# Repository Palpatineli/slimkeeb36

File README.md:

# Slimkeeb 36 wireless split ergo keyboard

This repo contains the PCB design files and the 3d printed case file for the keyboard.
You can find the firmware at [repo](https://github.com/Palpatineli/slimkeeb36-firmware).
In the [release page](https://github.com/Palpatineli/slimkeeb36/releases/latest) you can find the pre-compiled gerber file, the stl model file and the configured 3mf file.
For the keycap used in the above photo, I am using [CLP](https://github.com/vvhg1/clp-keycaps) which is similar to chicago steno.
However you can use any low profile mx keycap you like.

## Why

Compared to existing ergo keyboards, Slimkeeb36 can be a portable, beginner friendly, and cheap choice:

1. Portable. Slim 36-key wireless design, has a built-in travel mode with no need for cases.
2. Easy to assemble and repair. Diodeless. All parts on one side of pcb.
3. Long battery life
    - Seeed xiao + 10440 battery provides long battery life at low cost
4. More column stagger and protruding thumb cluster for extra ergonomics. Choc V2 switches offer more smooth options compared to choc V1.
5. Cheap for its features:
    - Minimal parts requirement. No diodes, no buttons, no screws or insets.
    - Double sided pcb, under 100x100mm, no castellation. Can be ordered on jlcpcb for <$3 per batch (excluding shipping and tariff).
    - Case can be easily printed at home.

## What

1. Download the gerber file or export from kicad files.
Make you PCB with online PCB vendors, such as [pcbway](https://www.pcbway.com/) or [jlcpcb](https://jlcpcb.com/).
The same PCB design works for both left and right halves.
Follow vendor's guide on gerber export [such as](https://www.pcbway.com/helpcenter/generate_gerber/Generate_Gerber_file_from_Kicad.html), since the format requirement can be different.
2. Order the following:
    - Your switches and keycaps.
    - 10440 battery X2 (not AAA! 10440 are 3.7V rechargeable batteries in the same form factor as AAA). I am using [these ones](https://www.amazon.com/Rechargeable-Battery-JESSPOW-Batteries-Flashlight/dp/B08H4RC1Y5).
    - Choc hotswap sockets X36, [such as](https://www.amazon.com/Mechkeeb-Kailh-Low-Hot-swappable-Socket/dp/B0BS3JYJJQ). It's the same one for choc v1 and v2.
    - Seeed Xiao nrf52840 X2, [such as](https://www.amazon.com/XIAO-nRF52840-3PCS-Pack-CircuitPython/dp/B0DJ6NZVJT). Make sure it's nrf52840 or BLE, not BLE sense or BLE plus. Do not buy the pre-soldered ones.
    - Some 24AWG stranded wire.
    - Some electric tape.
3. Tools you will need:
    - Soldering iron
    - Multimeter
    - Soldering wire or paste. Paste is probably easier for beginners. Use the small tip on the iron if you use paste.
    - Toothpicks or small tip tweezers
    - Scissors
    - Super glue
    - USB data cable
    - A basic FDM 3d printer, 0.4mm or 0.2mm nozzle. Either PLA or PETG can work.
        - If you don't have a printer that's fine. You can order the print from online vendors (the PCB vendors do 3d prints too).

## How

1. Use solder wire or very little paste to solder the seeed xiao on the PCB. If you use too much paste on seeed xiao the pads will short and it's hard to repair.
    
2. Use 4 pieces of wire to connect the 4 pads (battery+, battery-, NFC-1, NFC-2) to the corresponding pads on the PCB board.
3. Solder 2 pieces of wires to the innermost battery+ and battery- pads. Leave bare ends for battery. For best contact, leave a lot of bare end and roll it into a ball.
4. Solder the hotswaps. The easy way to solder them is simply to use a lot paste, but I should clean it up afterwards.
5. Use electric tapes to bind the battery+ and battery- bare wire ends to the battery.
    - If connected correctly, when you plugin the USB cable to seeed xiao, the green light will light up.
6. Test your board with a multimeter. Then flash the seeed xiao's, connect wirelessly to your computer, and test the keys now either by temporarily plugging in the switches, or just use barewire/tweezers.
7. Print your case.
    - You can just use the 3mf file for printing. It's set up for 0.2 nozzle, pla, high temp smooth 180mm plate.
    - Or you can use the stl files.
        - The 'top' parts needs to be cut at 6.4mm, then its bottom half flipped. The bottom half needs to have 100% infill and [bricklayer](https://github.com/TengerTechnologies/Bricklayers).
    - You can modify and run the `.py` file to get the stl file. Uncomment the last part if you need `.step` file for use in other modeling software. The only dependency is the `build123d` package.
        - You can reduce the h['key'] if you only plan to use flat keycaps.
8. Assembly:
    1. Check the switch openings. Sometimes the first layer is overextruded and you need to trim it down or the switches will not fit.
    2. Use super glue to attach battery compartment and shroud to the top cover.
    3. Carefully insert the battery into the grove, with the attached wire on the deeper side.
    4. Aim to board to the opening on the bottom part. Snap close the case.
    5. Install your switches and keycaps.

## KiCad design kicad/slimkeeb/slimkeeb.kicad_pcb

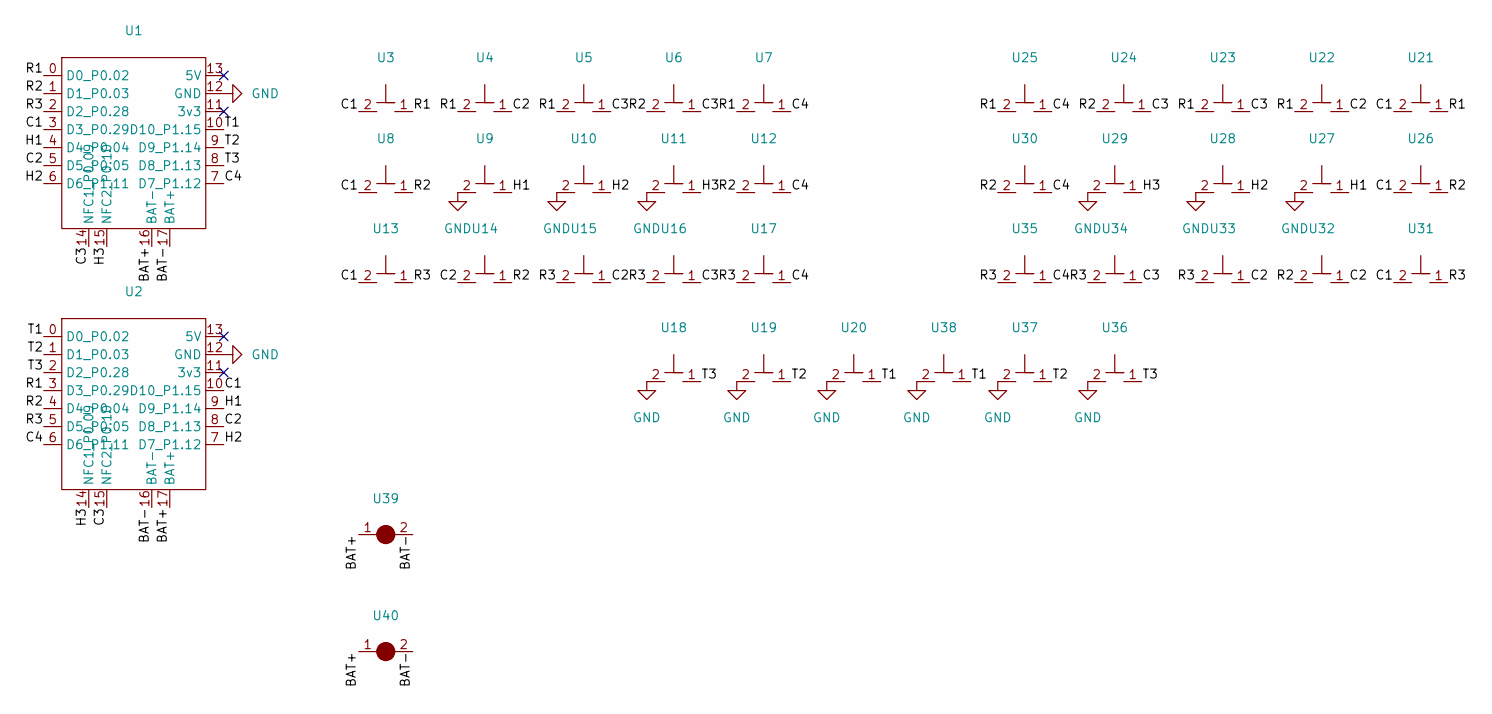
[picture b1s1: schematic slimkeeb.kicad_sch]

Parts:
U1, U2: seeed xiao nRF52840_reverse
U3, U4, U5, U6, U7, U8, U9, U10, U11, U12, U13, U14, U15, U16, U17, U18, U19, U20, U21, U22, U23, U24, U25, U26, U27, U28, U29, U30, U31, U32, U33, U34, U35, U36, U37, U38: choc_v2_swap
U39, U40: wide_jumper

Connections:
/BAT+: U1.16 (BAT-), U2.17 (BAT+), U39.1, U40.1
/BAT-: U1.17 (BAT+), U2.16 (BAT-), U39.2, U40.2
/C1: U1.3 (D3_P0.29), U2.10 (D10_P1.15), U3.2, U8.2, U13.2, U21.2, U26.2, U31.2
/C2: U1.5 (D5_P0.05), U2.8 (D8_P1.13), U4.1, U14.2, U15.1, U22.1, U32.1, U33.1
/C3: U1.14 (NFC1_P0.09), U2.15 (NFC2_P0.10), U5.1, U6.1, U16.1, U23.1, U24.1, U34.1
/C4: U1.7 (D7_P1.12), U2.6 (D6_P1.11), U7.1, U12.1, U17.1, U25.1, U30.1, U35.1
/H1: U1.4 (D4_P0.04), U2.9 (D9_P1.14), U9.1, U27.1
/H2: U1.6 (D6_P1.11), U2.7 (D7_P1.12), U10.1, U28.1
/H3: U1.15 (NFC2_P0.10), U2.14 (NFC1_P0.09), U11.1, U29.1
/R1: U1.0 (D0_P0.02), U2.3 (D3_P0.29), U3.1, U4.2, U5.2, U7.2, U21.1, U22.2, U23.2, U25.2
/R2: U1.1 (D1_P0.03), U2.4 (D4_P0.04), U6.2, U8.1, U12.2, U14.1, U24.2, U26.1, U30.2, U32.2
/R3: U1.2 (D2_P0.28), U2.5 (D5_P0.05), U13.1, U15.2, U16.2, U17.2, U31.1, U33.2, U34.2, U35.2
/T1: U1.10 (D10_P1.15), U2.0 (D0_P0.02), U20.1, U38.1
/T2: U1.9 (D9_P1.14), U2.1 (D1_P0.03), U19.1, U37.1
/T3: U1.8 (D8_P1.13), U2.2 (D2_P0.28), U18.1, U36.1
GND: U1.12 (GND), U2.12 (GND), U9.2, U10.2, U11.2, U18.2, U19.2, U20.2, U27.2, U28.2, U29.2, U36.2, U37.2, U38.2

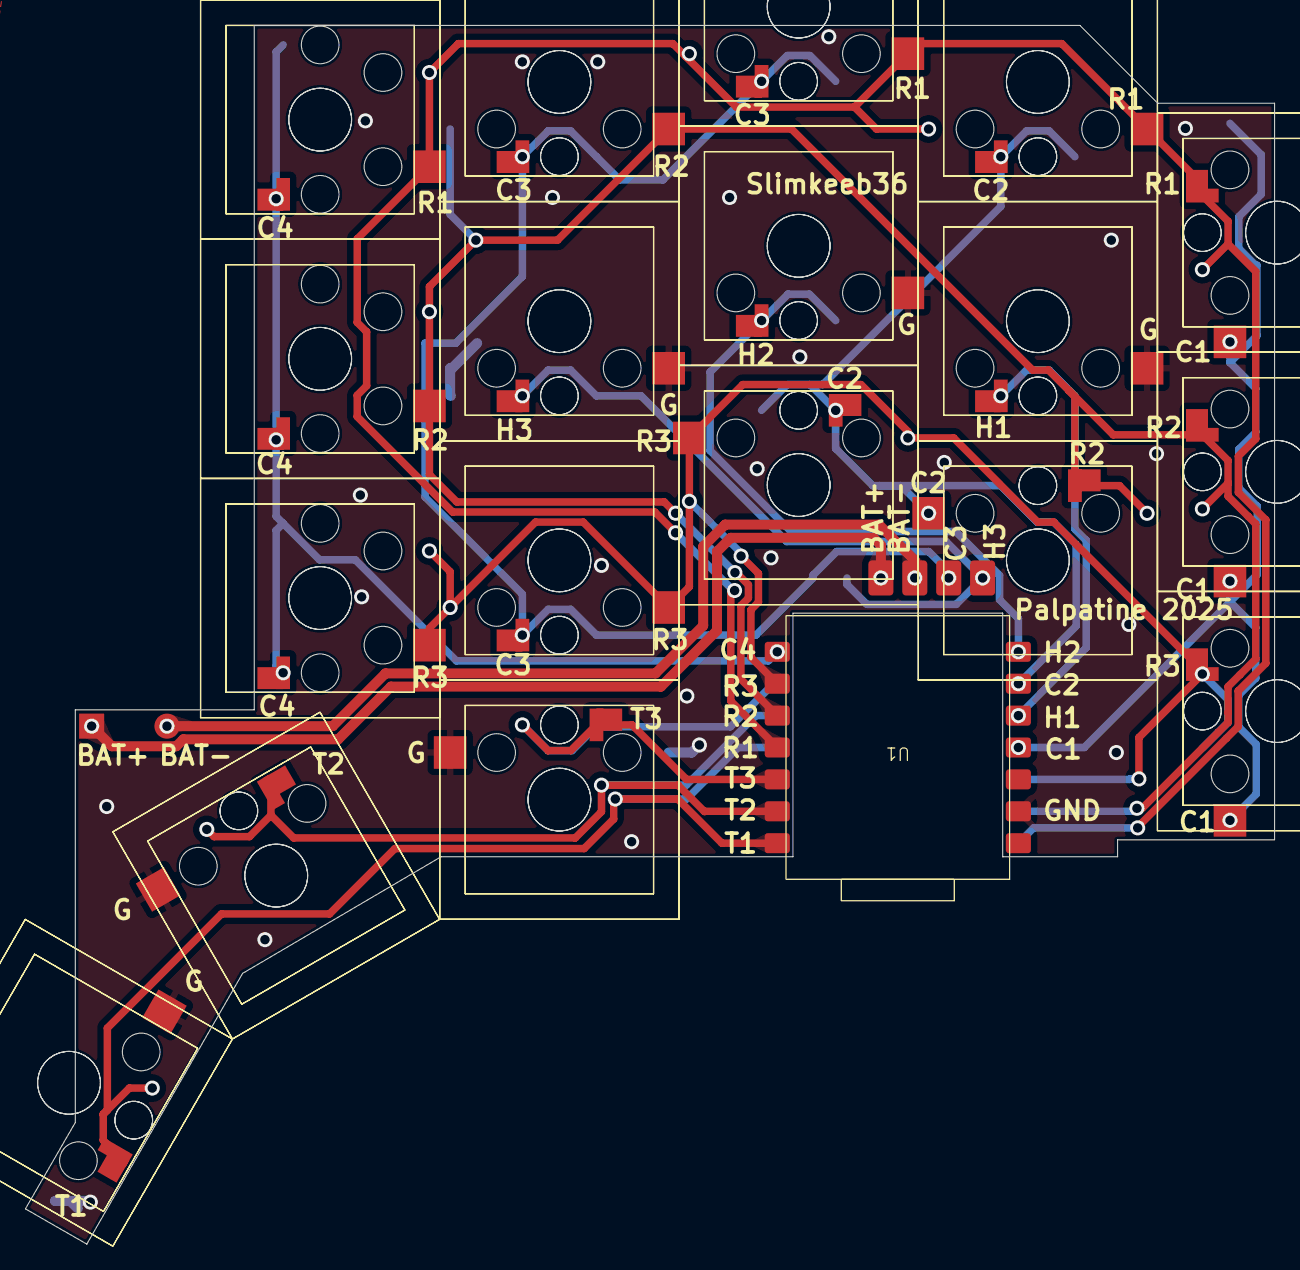
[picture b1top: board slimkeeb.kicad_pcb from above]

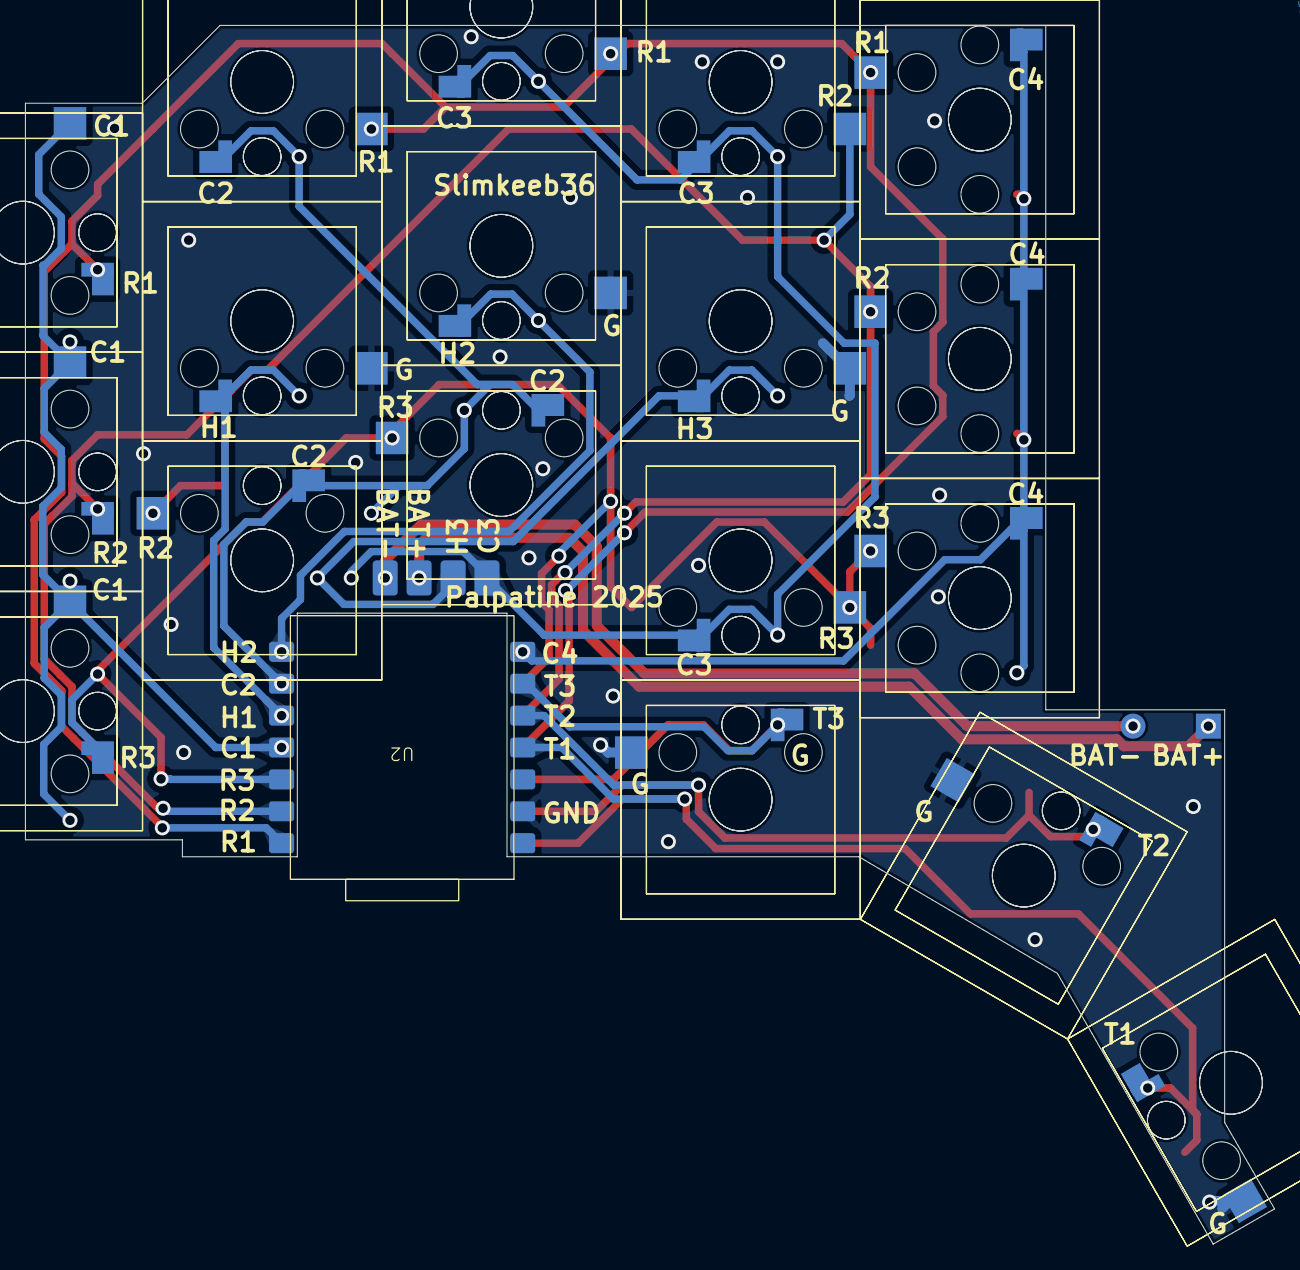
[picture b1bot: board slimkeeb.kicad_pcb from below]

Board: 2 copper layers, 99.5 x 97.0 mm, 40 parts (20 on the bottom side), 16 nets.

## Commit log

2025-07-01 feat: add readme
